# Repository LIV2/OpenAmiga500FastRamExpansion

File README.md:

# OpenAmiga500FastRamExpansion
OpenAmiga500FastRamExpansion is an Open Hardware 4/8 MB Fast RAM Expansion for the Commodore Amiga 500 Computer.

### Summary
Most low-end Amiga models only came with *Chip RAM*. "Big Box" models allowed for a different type of memory to be installed, known as *Fast RAM*, where *fast* means that it's dedicated to the main processor, so that it doesn't have to compete with the other chips in order to gain access to it (as is the case with Chip RAM). While both Chip and Fast RAM are limited in size, you can have at least a few MB of the latter on all Amigas (usually up to 8), while the former can never exceed 2 MB.

OpenAmiga500FastRamExpansion will allow you to add 4 or 8 MB of Fast RAM to your Amiga 500. This way you will be able to run more applications at once and more quickly. If you combine it with [a chip RAM expansion](http://eab.abime.net/showthread.php?t=85395), you will also be able to run almost all games supported by WHDLoad, pushing your Amiga to its limits.

OpenAmiga500FastRamExpansion is basically a clone of [a RAM expansion produced by Kipper2K a few years ago](http://eab.abime.net/showthread.php?t=64218), based on [an earlier design by lvd/NedoPC](http://lvd.nedopc.com/Projects/a600_8mb/index.html). He has since stopped producing and selling these cards and I thought it was a pity that he didn't open his designs and actually took all of them down, as this card is quite cheap to build and really useful. So I set about recreating it from scratch.

### Memory Compatibility
The required RAM Type is 16 Mbit (1M×16) DRAM in the SOJ-42 package with up to 70-80 ns access time. It is 5v-only DRAM (not SD(!)RAM) often found in old 72-pin SIMMs, EDO chips might work or not. All chips having *8160* in their part number should be OK.

|Model          |Maker             |Tested             |Working            |Data Sheet                                                                                                                                                                 |Notes                                                                                |
|---------------|------------------|:-----------------:|:-----------------:|:-------------------------------------------------------------------------------------------------------------------------------------------------------------------------:|-------------------------------------------------------------------------------------|
|AS4C1M116E5    |Alliance          |||                                                                                                                                                                           |Tested by @Homer799                                                                  |
|GM71C18160     |Hynix/LGS         |||                                                                    |Tested by lvd in his original project                                                |
|HY5118164B     |Hynix             |||                                                                                                                                                                           |Tested by @Sgw32                                                                     |
|KM416C1200AJ   |SEC               |||                                                                                                                                                                           |Reported working by Ronald Baer                                                      |
|KM416C1204AJ/BJ|SEC               |||                                             |Reported working by screwbreaker                                                     |
|MSM5118160     |OKI               |||                                                                    |Tested by lvd in his original project                                                |
|TMS41860DZ     |Texas Instruments |||                                                                                                                                                                           |Reported working by Ronald Baer                                                      |
|TMS41869DZ     |Texas Instruments |  |                   |                                                                                                                                                                           |                                                                                     |
|4218160        |NEC               |||                                                                                                                                                                           |Reported working by Ronald Baer                                                      |
|4218165        |NEC               |||                          |Tested by SukkoPera                                                                  |
|VG2618165BJ    |Vanguard          |||                                                                                                                                                                           |Tested by @Csordi                                                                    |
|NN5118160AJ-60 |NPN               |||                                                                                                                                                                           |Tested by @RipZ                                                                      |

RAM chips can either be soldered directly to the board or installed in sockets. While soldering the chips might not be trivial for the unexperienced, sockets for the SOJ-42 package are hard to find and not really easier to solder either, so the choice is up to you.

### Assembly and Installation
Normally it is not necessary to mount all the decoupling capacitors. I usually skip C4, C5, C9, C12, C15 and C18. Maybe C1 can be left out as well if you have a good power supply, your choice. R4 must be chosen according to the particular led you will be using for LD1. Actually you are free to skip LD1 and R4 altogether, if you hate power LEDs.

After everything has been soldered, you will need to program the CPLD. Whenever you do so, **make sure to carefully remove the board from your Amiga, or you might risk damaging it**. You can find the firmware [here](firmware/V2), along with instructions on how to flash it. You can provide power through the pads of C1 if you need to do so.

Make sure to use the [correct firmware version](#Firmware), according to how many chips you soldered on the board! For the 4 MB version, solder U7 and U8 only and use the dedicated firmware.

When assembly is complete, open your A500 and remove the top shield. Carefully remove the CPU (largest chip at bottom left of the board), using a chip extractor or a small flat screwdriver, taking care not to break/bend any pins. Plug it on the board, matching the orientation, and plug the whole board in the CPU socket.

Before reassembling your case, I recommend to run [SysTest/Amiga Test Kit](https://github.com/keirf/Amiga-Stuff). Use the Memory option (<kbd>F1</kbd>), it must show 4/8 MB of Fast RAM. Then start the Memory Test (<kbd>F1</kbd> again) and let it run for 50-100 rounds: if it doesn't find any errors, you are probably good to go. If you get any errors, check your solder joints, starting from actual the RAM chips, as the SOJ package is not very hand-soldering-friendly.

### Firmware
If you are using Kickstart 2.x or higher you should use the latest V2 firmware [here](firmware/V2) noting that it requires an ATF1504AS rather than the older version's ATF1502

If you are using Kickstart 1.3 you will need to use the [V1 Firmware here](firmware/V1)

#### V2 Firmware new features
Thanks to two new features this board is compatible with other autoconfig devices and should no longer cause any conflicts
* Autoconfig snooping - This board will configure itself after every other Autoconfig device
* Autosizing - The firmware will shrink the configured size automatically to make it fit within the remaining free memory pool (8M/4M/2M/1M).

#### V1 Firmware Limitations
The V1 Firmware for OpenAmiga500FastRamExpansion only has a partial implementation of the AutoConfig protocol. This has the following consequences:
- On the A500 it will only work if nothing is connected to the side expansion port (or if whatever is connected does NOT use AutoConfig).
- On the A2000 it will only work if nothing is installed in the Zorro expansion slots (again: or if whatever you installed there does not use AutoConfig).
- On the CDTV it just won't work (since the DMAC uses AutoConfig and is built-in.)

Because of these limitations it is recommended to use the new Firmware where possible, this will allow your board to coexist with other Autoconfig devices.
If you cannot use the V2 firmware for some reason (i.e you use Kickstart 1.3) then the only way to get around these limitations is flashing an alternative firmware on the board which does not use AutoConfig, but then you will have to add the RAM manually in Workbench, using the `addmem` utility. More on this soon.

### License
The OpenAmiga500FastRamExpansion documentation, including the design itself, is copyright &copy; SukkoPera 2019.

OpenAmiga500FastRamExpansion is Open Hardware licensed under the [CERN OHL v. 1.2](http://ohwr.org/cernohl).

You may redistribute and modify this documentation under the terms of the CERN OHL v.1.2. This documentation is distributed *as is* and WITHOUT ANY EXPRESS OR IMPLIED WARRANTIES whatsoever with respect to its functionality, operability or use, including, without limitation, any implied warranties OF MERCHANTABILITY, SATISFACTORY QUALITY, FITNESS FOR A PARTICULAR PURPOSE or infringement. We expressly disclaim any liability whatsoever for any direct, indirect, consequential, incidental or special damages, including, without limitation, lost revenues, lost profits, losses resulting from business interruption or loss of data, regardless of the form of action or legal theory under which the liability may be asserted, even if advised of the possibility or likelihood of such damages.

A copy of the full license is included in file [LICENSE.pdf](LICENSE.pdf), please refer to it for applicable conditions. In order to properly deal with its terms, please see file [LICENSE_HOWTO.pdf](LICENSE_HOWTO.pdf).

The contact points for information about manufactured Products (see section 4.2) are listed in file [PRODUCT.md](PRODUCT.md).

Any modifications made by Licensees (see section 3.4.b) shall be recorded in file [CHANGES.md](CHANGES.md).

The Documentation Location of the original project is https://github.com/SukkoPera/OpenAmiga500FastRamExpansion/.

### Support the Project
Since the project is open you are free to get the PCBs made by your preferred manufacturer, however in case you want to support the development, you can order them from PCBWay through this link:

You get my gratitude and cheap, professionally-made and good quality PCBs, I get some credit that will help with this and [other projects](https://www.pcbway.com/project/member/shareproject/?bmbid=41100). You won't even have to worry about the various PCB options, it's all pre-configured for you!

Also, if you still have to register to that site, [you can use this link](https://www.pcbway.com/setinvite.aspx?inviteid=41100) to get some bonus initial credit (and yield me some more).

Again, if you want to use another manufacturer, feel free to, don't feel obligated :). But then you can buy me a coffee if you want:

### Thanks
- lvd for the initial design and the support he gave me during development
- Kipper2K for making his boards
- majinga for helping with the testing

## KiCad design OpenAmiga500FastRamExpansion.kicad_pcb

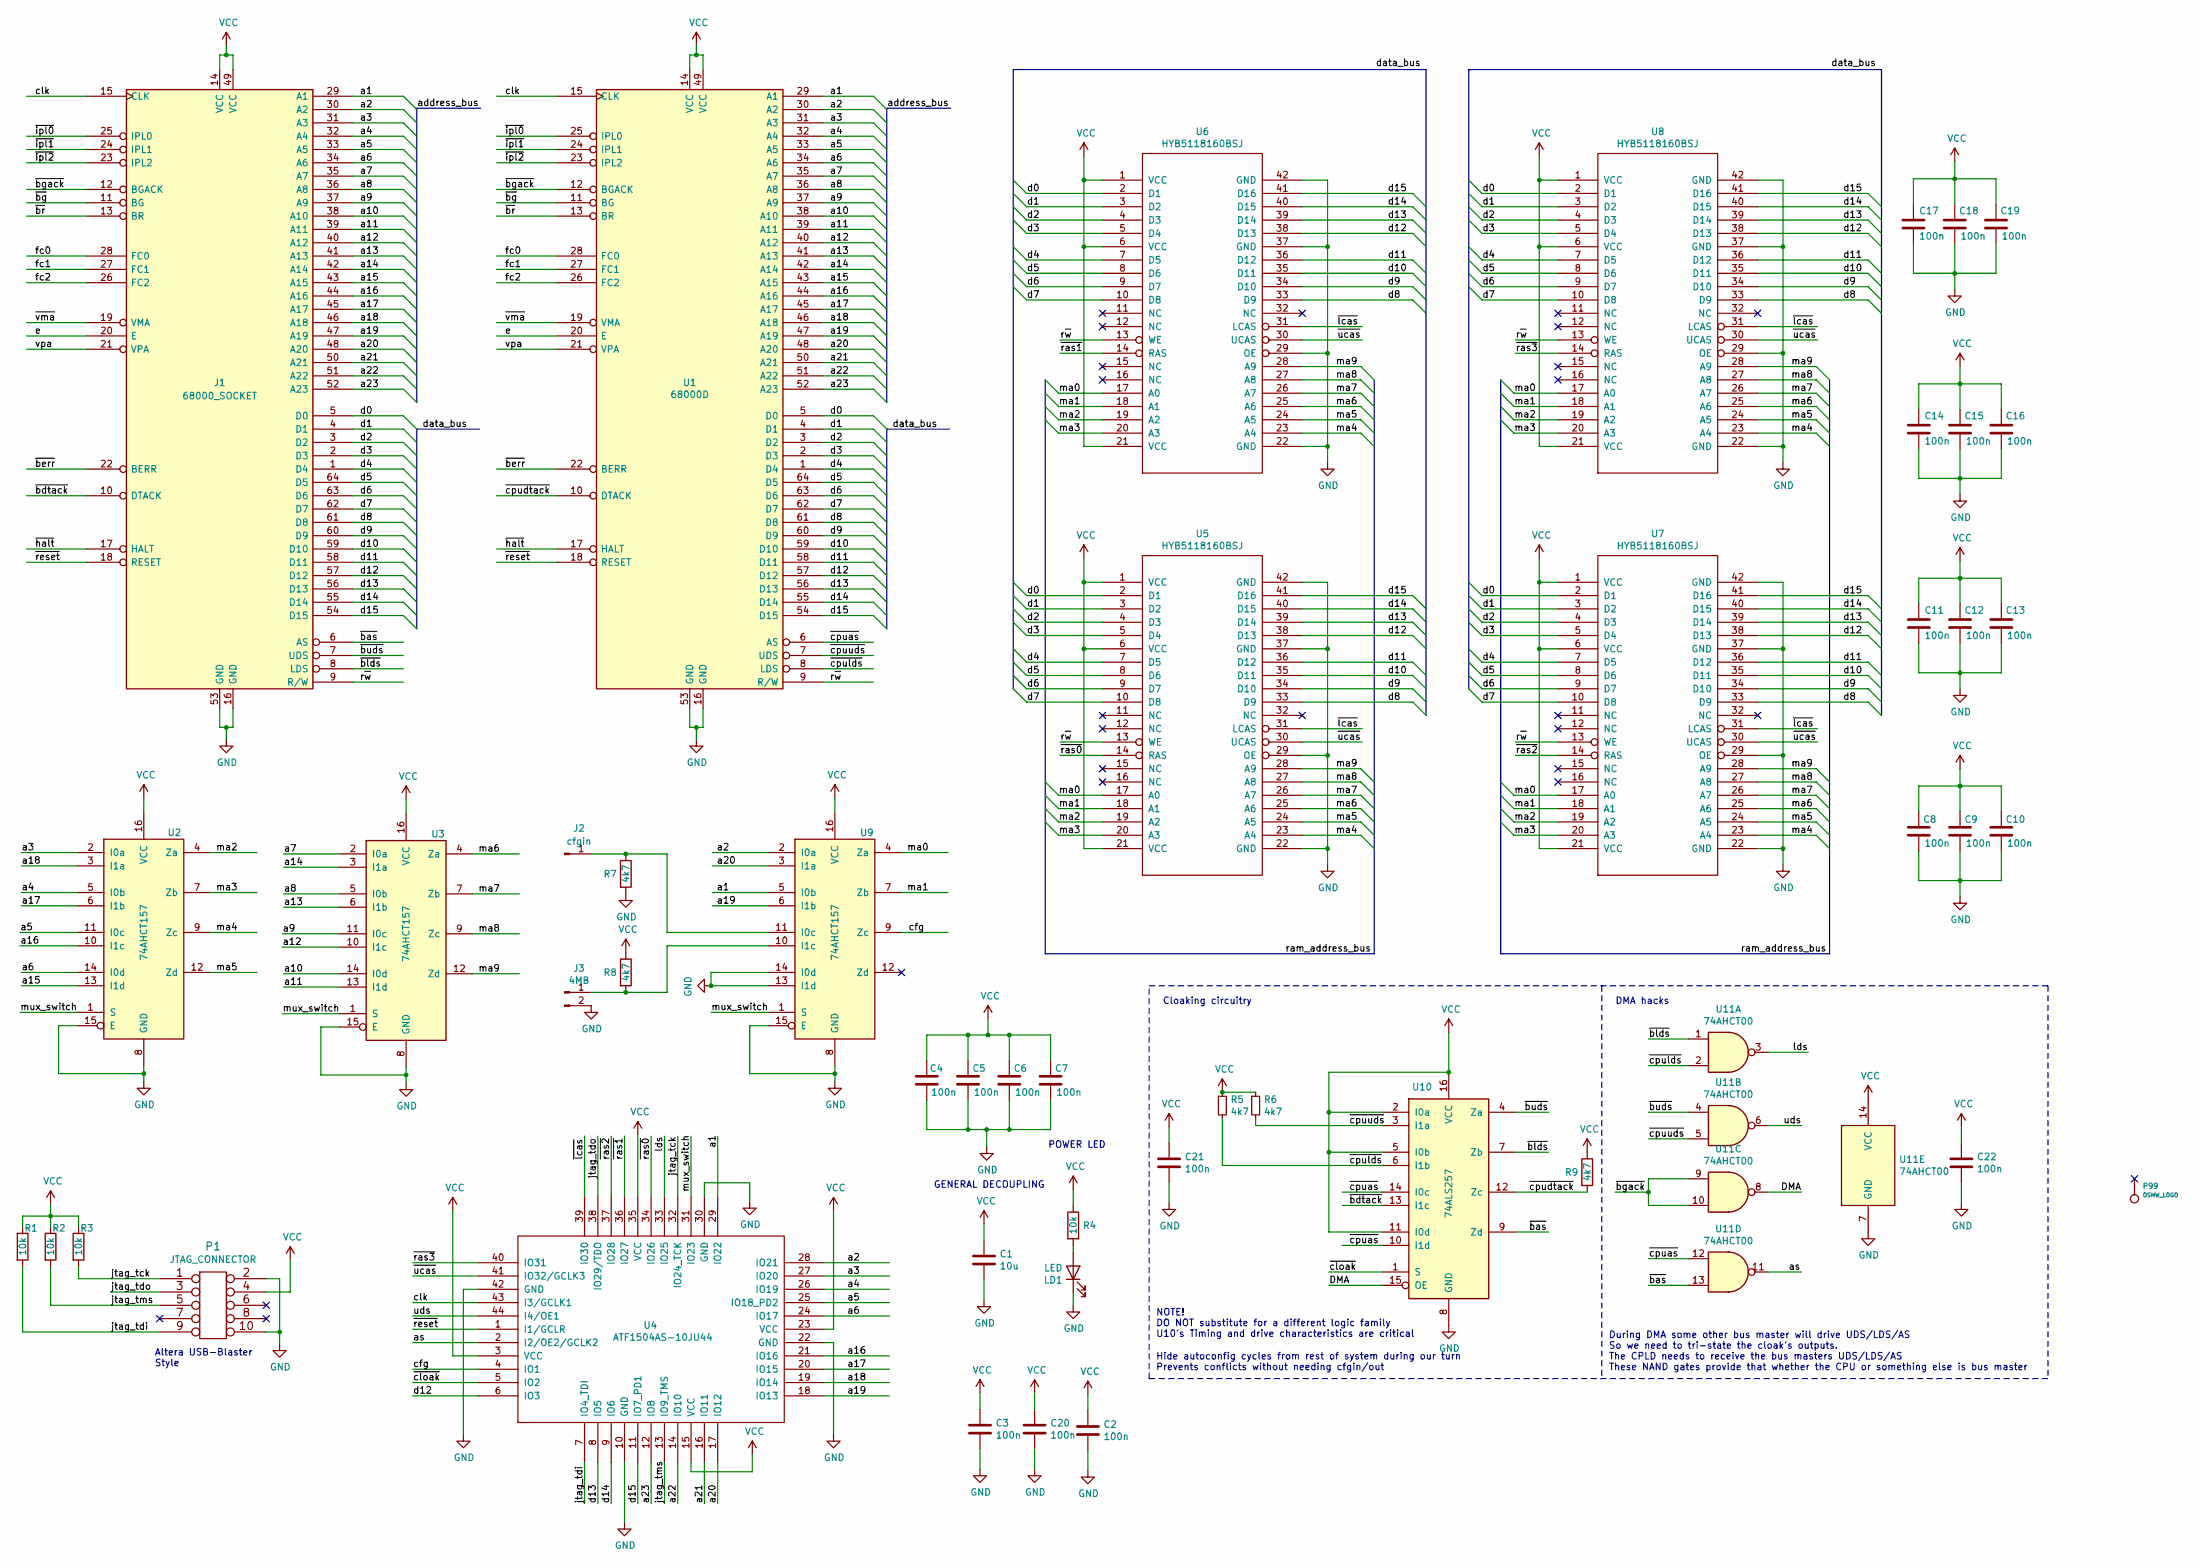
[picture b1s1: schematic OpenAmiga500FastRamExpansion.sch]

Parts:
C1: 10u; CP_Radial_D5.0mm_P2.00mm
C2, C3, C4, C5, C6, C7, C8, C9, C10, C11, C12, C13, C14, C15, C16, C17, C18, C19: 100n; C_0805_2012Metric_Pad1.15x1.40mm_HandSolder
C20, C21, C22: 100n; C_0805_2012Metric_Pad1.18x1.45mm_HandSolder
J1: 68000_SOCKET; DIP-64_W22.86mm_Socket_LongPads_Socket
J2: cfgin; PinHeader_1x01_P2.54mm_Horizontal
J3: 4MB; PinHeader_1x02_P2.54mm_Horizontal
LD1: LED; LED_0805_HandSoldering_ModSilkS
P1: JTAG_CONNECTOR; IDC-Header_2x05_P2.54mm_Vertical
P99: OSHW_LOGO; OSHW-Logo2_7.3x6mm_Copper
R1, R2, R3, R4: 10k; R_0805_2012Metric_Pad1.15x1.40mm_HandSolder
R5, R6, R7, R8, R9: 4k7; R_0805_2012Metric_Pad1.20x1.40mm_HandSolder
U1: 68000D; DIP-64_W22.86mm_Socket_LongPads_IC
U2, U3, U9: 74AHCT157; SOIC-16_3.9x9.9mm_P1.27mm
U4: ATF1504AS-10JU44; PLCC-44_THT-Socket
U5, U6, U7, U8: HYB5118160BSJ; SOJ-42-LongPads
U10: 74ALS257; SOIC-16_3.9x9.9mm_P1.27mm
U11: 74AHCT00; SOIC-14_3.9x8.7mm_P1.27mm

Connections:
/DMA: U10.15 (OE), U11.8
/a1: J1.29 (A1), U1.29 (A1), U4.29 (IO22), U9.5 (I0b)
/a2: J1.30 (A2), U1.30 (A2), U4.28 (IO21), U9.2 (I0a)
/a3: J1.31 (A3), U1.31 (A3), U2.2 (I0a), U4.27 (IO20)
/a4: J1.32 (A4), U1.32 (A4), U2.5 (I0b), U4.26 (IO19)
/a5: J1.33 (A5), U1.33 (A5), U2.11 (I0c), U4.25 (IO18_PD2)
/a6: J1.34 (A6), U1.34 (A6), U2.14 (I0d), U4.24 (IO17)
/a7: J1.35 (A7), U1.35 (A7), U3.2 (I0a)
/a8: J1.36 (A8), U1.36 (A8), U3.5 (I0b)
/a9: J1.37 (A9), U1.37 (A9), U3.11 (I0c)
/a10: J1.38 (A10), U1.38 (A10), U3.14 (I0d)
/a11: J1.39 (A11), U1.39 (A11), U3.13 (I1d)
/a12: J1.40 (A12), U1.40 (A12), U3.10 (I1c)
/a13: J1.41 (A13), U1.41 (A13), U3.6 (I1b)
/a14: J1.42 (A14), U1.42 (A14), U3.3 (I1a)
/a15: J1.43 (A15), U1.43 (A15), U2.13 (I1d)
/a16: J1.44 (A16), U1.44 (A16), U2.10 (I1c), U4.21 (IO16)
/a17: J1.45 (A17), U1.45 (A17), U2.6 (I1b), U4.20 (IO15)
/a18: J1.46 (A18), U1.46 (A18), U2.3 (I1a), U4.19 (IO14)
/a19: J1.47 (A19), U1.47 (A19), U4.18 (IO13), U9.6 (I1b)
/a20: J1.48 (A20), U1.48 (A20), U4.17 (IO12), U9.3 (I1a)
/a21: J1.50 (A21), U1.50 (A21), U4.16 (IO11)
/a22: J1.51 (A22), U1.51 (A22), U4.14 (IO10)
/a23: J1.52 (A23), U1.52 (A23), U4.12 (IO8)
/as: U4.2 (I2/OE2/GCLK2), U11.11
/cfg: U4.4 (IO1), U9.9 (Zc)
/clk: J1.15 (CLK), U1.15 (CLK), U4.43 (I3/GCLK1)
/d0: J1.5 (D0), U1.5 (D0), U5.2 (D1), U6.2 (D1), U7.2 (D1), U8.2 (D1)
/d1: J1.4 (D1), U1.4 (D1), U5.3 (D2), U6.3 (D2), U7.3 (D2), U8.3 (D2)
/d2: J1.3 (D2), U1.3 (D2), U5.4 (D3), U6.4 (D3), U7.4 (D3), U8.4 (D3)
/d3: J1.2 (D3), U1.2 (D3), U5.5 (D4), U6.5 (D4), U7.5 (D4), U8.5 (D4)
/d4: J1.1 (D4), U1.1 (D4), U5.7 (D5), U6.7 (D5), U7.7 (D5), U8.7 (D5)
/d5: J1.64 (D5), U1.64 (D5), U5.8 (D6), U6.8 (D6), U7.8 (D6), U8.8 (D6)
/d6: J1.63 (D6), U1.63 (D6), U5.9 (D7), U6.9 (D7), U7.9 (D7), U8.9 (D7)
/d7: J1.62 (D7), U1.62 (D7), U5.10 (D8), U6.10 (D8), U7.10 (D8), U8.10 (D8)
/d8: J1.61 (D8), U1.61 (D8), U5.33 (D9), U6.33 (D9), U7.33 (D9), U8.33 (D9)
/d9: J1.60 (D9), U1.60 (D9), U5.34 (D10), U6.34 (D10), U7.34 (D10), U8.34 (D10)
/d10: J1.59 (D10), U1.59 (D10), U5.35 (D11), U6.35 (D11), U7.35 (D11), U8.35 (D11)
/d11: J1.58 (D11), U1.58 (D11), U5.36 (D12), U6.36 (D12), U7.36 (D12), U8.36 (D12)
/d12: J1.57 (D12), U1.57 (D12), U4.6 (IO3), U5.38 (D13), U6.38 (D13), U7.38 (D13), U8.38 (D13)
/d13: J1.56 (D13), U1.56 (D13), U4.8 (IO5), U5.39 (D14), U6.39 (D14), U7.39 (D14), U8.39 (D14)
/d14: J1.55 (D14), U1.55 (D14), U4.9 (IO6), U5.40 (D15), U6.40 (D15), U7.40 (D15), U8.40 (D15)
/d15: J1.54 (D15), U1.54 (D15), U4.11 (IO7_PD1), U5.41 (D16), U6.41 (D16), U7.41 (D16), U8.41 (D16)
/e: J1.20 (E), U1.20 (E)
/fc0: J1.28 (FC0), U1.28 (FC0)
/fc1: J1.27 (FC1), U1.27 (FC1)
/fc2: J1.26 (FC2), U1.26 (FC2)
/jtag_tck: P1.1, R3.2, U4.32 (IO24_TCK)
/jtag_tdi: P1.9, R1.2, U4.7 (IO4_TDI)
/jtag_tdo: P1.3, U4.38 (IO29/TDO)
/jtag_tms: P1.5, R2.2, U4.13 (IO9_TMS)
/lds: U4.33 (IO25), U11.3
/ma0: U5.17 (A0), U6.17 (A0), U7.17 (A0), U8.17 (A0), U9.4 (Za)
/ma1: U5.18 (A1), U6.18 (A1), U7.18 (A1), U8.18 (A1), U9.7 (Zb)
/ma2: U2.4 (Za), U5.19 (A2), U6.19 (A2), U7.19 (A2), U8.19 (A2)
/ma3: U2.7 (Zb), U5.20 (A3), U6.20 (A3), U7.20 (A3), U8.20 (A3)
/ma4: U2.9 (Zc), U5.23 (A4), U6.23 (A4), U7.23 (A4), U8.23 (A4)
/ma5: U2.12 (Zd), U5.24 (A5), U6.24 (A5), U7.24 (A5), U8.24 (A5)
/ma6: U3.4 (Za), U5.25 (A6), U6.25 (A6), U7.25 (A6), U8.25 (A6)
/ma7: U3.7 (Zb), U5.26 (A7), U6.26 (A7), U7.26 (A7), U8.26 (A7)
/ma8: U3.9 (Zc), U5.27 (A8), U6.27 (A8), U7.27 (A8), U8.27 (A8)
/ma9: U3.12 (Zd), U5.28 (A9), U6.28 (A9), U7.28 (A9), U8.28 (A9)
/mux_switch: U2.1 (S), U3.1 (S), U4.31 (IO23), U9.1 (S)
/r~w: J1.9 (R/W), U1.9 (R/W), U5.13 (WE), U6.13 (WE), U7.13 (WE), U8.13 (WE)
/uds: U4.44 (I4/OE1), U11.6
/vpa: J1.21 (VPA), U1.21 (VPA)
/~bas: J1.6 (AS), U10.9 (Zd), U11.13
/~bdtack: J1.10 (DTACK), U10.13 (I1c)
/~berr: J1.22 (BERR), U1.22 (BERR)
/~bg: J1.11 (BG), U1.11 (BG)
/~bgack: J1.12 (BGACK), U1.12 (BGACK), U11.9, U11.10
/~blds: J1.8 (LDS), U10.7 (Zb), U11.1
/~br: J1.13 (BR), U1.13 (BR)
/~buds: J1.7 (UDS), U10.4 (Za), U11.4
/~cloak: U4.5 (IO2), U10.1 (S)
/~cpuas: U1.6 (AS), U10.10 (I1d), U10.14 (I0c), U11.12
/~cpudtack: R9.2, U1.10 (DTACK), U10.12 (Zc)
/~cpulds: R5.2, U1.8 (LDS), U10.6 (I1b), U11.2
/~cpuuds: R6.2, U1.7 (UDS), U10.3 (I1a), U11.5
/~halt: J1.17 (HALT), U1.17 (HALT)
/~ipl0: J1.25 (IPL0), U1.25 (IPL0)
/~ipl1: J1.24 (IPL1), U1.24 (IPL1)
/~ipl2: J1.23 (IPL2), U1.23 (IPL2)
/~lcas: U4.39 (IO30), U5.31 (LCAS), U6.31 (LCAS), U7.31 (LCAS), U8.31 (LCAS)
/~ras0: U4.34 (IO26), U5.14 (RAS)
/~ras1: U4.36 (IO27), U6.14 (RAS)
/~ras2: U4.37 (IO28), U7.14 (RAS)
/~ras3: U4.40 (IO31), U8.14 (RAS)
/~reset: J1.18 (RESET), U1.18 (RESET), U4.1 (I1/GCLR)
/~ucas: U4.41 (IO32/GCLK3), U5.30 (UCAS), U6.30 (UCAS), U7.30 (UCAS), U8.30 (UCAS)
/~vma: J1.19 (VMA), U1.19 (VMA)
GND: C1.2, C2.2, C3.2, C4.2, C5.2, C6.2, C7.2, C8.2, C9.2, C10.2, C11.2, C12.2, C13.2, C14.2, C15.2, C16.2, C17.2, C18.2, C19.2, C20.2, C21.2, C22.2, J1.16 (GND), J1.53 (GND), J3.2, LD1.1 (K), P1.2, P1.10, R7.2, U1.16 (GND), U1.53 (GND), U2.8 (GND), U2.15 (E), U3.8 (GND), U3.15 (E), U4.10 (GND), U4.22 (GND), U4.30 (GND), U4.42 (GND), U5.22 (GND), U5.29 (OE), U5.37 (GND), U5.42 (GND), U6.22 (GND), U6.29 (OE), U6.37 (GND), U6.42 (GND), U7.22 (GND), U7.29 (OE), U7.37 (GND), U7.42 (GND), U8.22 (GND), U8.29 (OE), U8.37 (GND), U8.42 (GND), U9.8 (GND), U9.13 (I1d), U9.14 (I0d), U9.15 (E), U10.8 (GND), U11.7 (GND)
unnamed: J2.1, R7.1, U9.11 (I0c)
unnamed: J3.1, R8.2, U9.10 (I1c)
unnamed: LD1.2 (A), R4.2
VCC: C1.1, C2.1, C3.1, C4.1, C5.1, C6.1, C7.1, C8.1, C9.1, C10.1, C11.1, C12.1, C13.1, C14.1, C15.1, C16.1, C17.1, C18.1, C19.1, C20.1, C21.1, C22.1, J1.14 (VCC), J1.49 (VCC), P1.4, R1.1, R2.1, R3.1, R4.1, R5.1, R6.1, R8.1, R9.1, U1.14 (VCC), U1.49 (VCC), U2.16 (VCC), U3.16 (VCC), U4.3 (VCC), U4.15 (VCC), U4.23 (VCC), U4.35 (VCC), U5.1 (VCC), U5.6 (VCC), U5.21 (VCC), U6.1 (VCC), U6.6 (VCC), U6.21 (VCC), U7.1 (VCC), U7.6 (VCC), U7.21 (VCC), U8.1 (VCC), U8.6 (VCC), U8.21 (VCC), U9.16 (VCC), U10.2 (I0a), U10.5 (I0b), U10.11 (I0d), U10.16 (VCC), U11.14 (VCC)

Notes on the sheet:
Altera USB-Blaster Style
Cloaking circuitry
DMA hacks
Hide autoconfig cycles from rest of system during our turn Prevents conflicts without needing cfgin/out
During DMA some other bus master will drive UDS/LDS/AS So we need to tri-state the cloak's outputs. The CPLD needs to receive the bus masters UDS/LDS/AS These NAND gates provide that whether the CPU or something else is bus master
GENERAL DECOUPLING
POWER LED
NOTE! DO NOT substitute for a different logic family U10's Timing and drive characteristics are critical

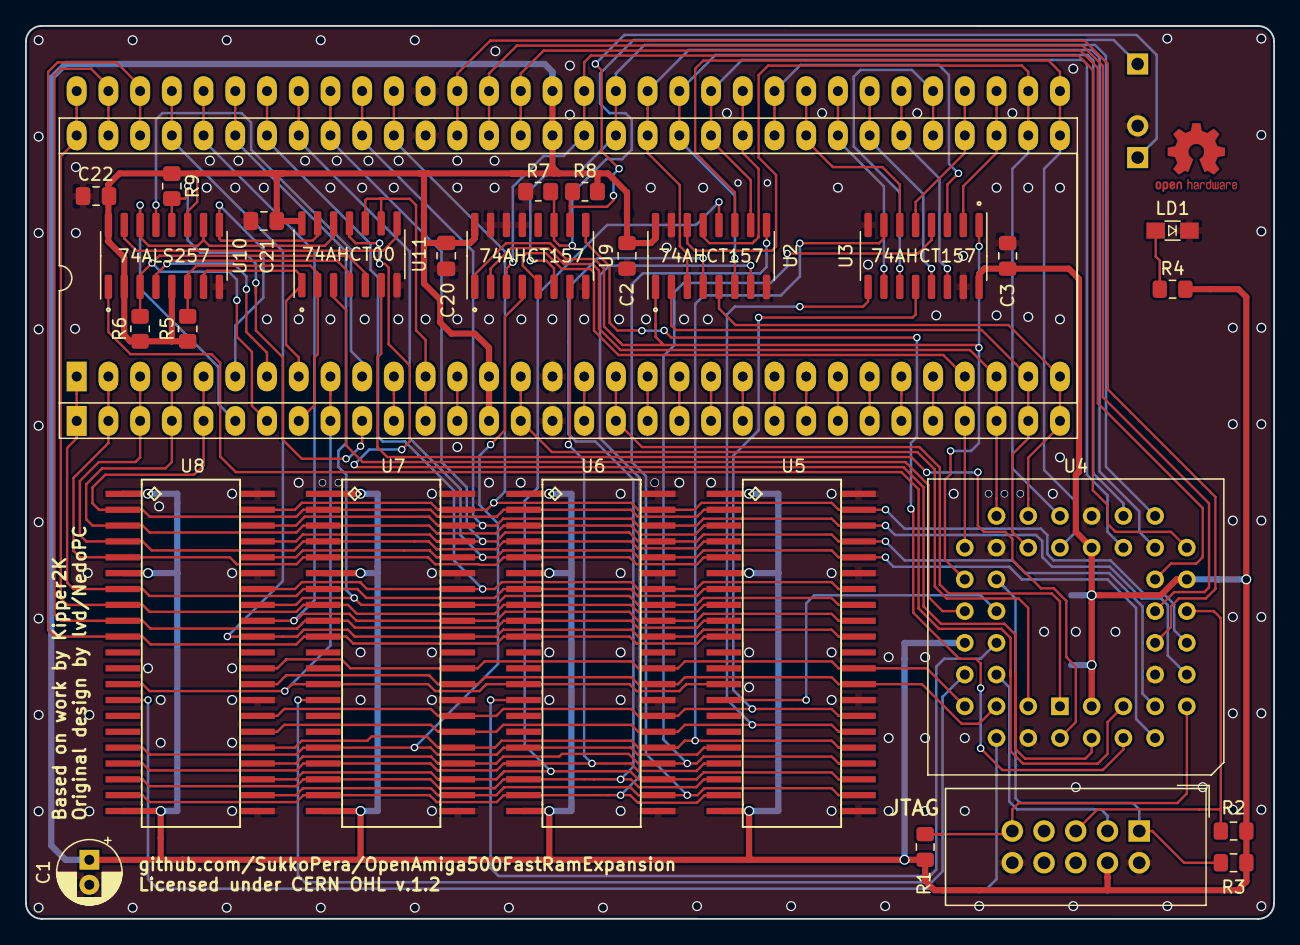
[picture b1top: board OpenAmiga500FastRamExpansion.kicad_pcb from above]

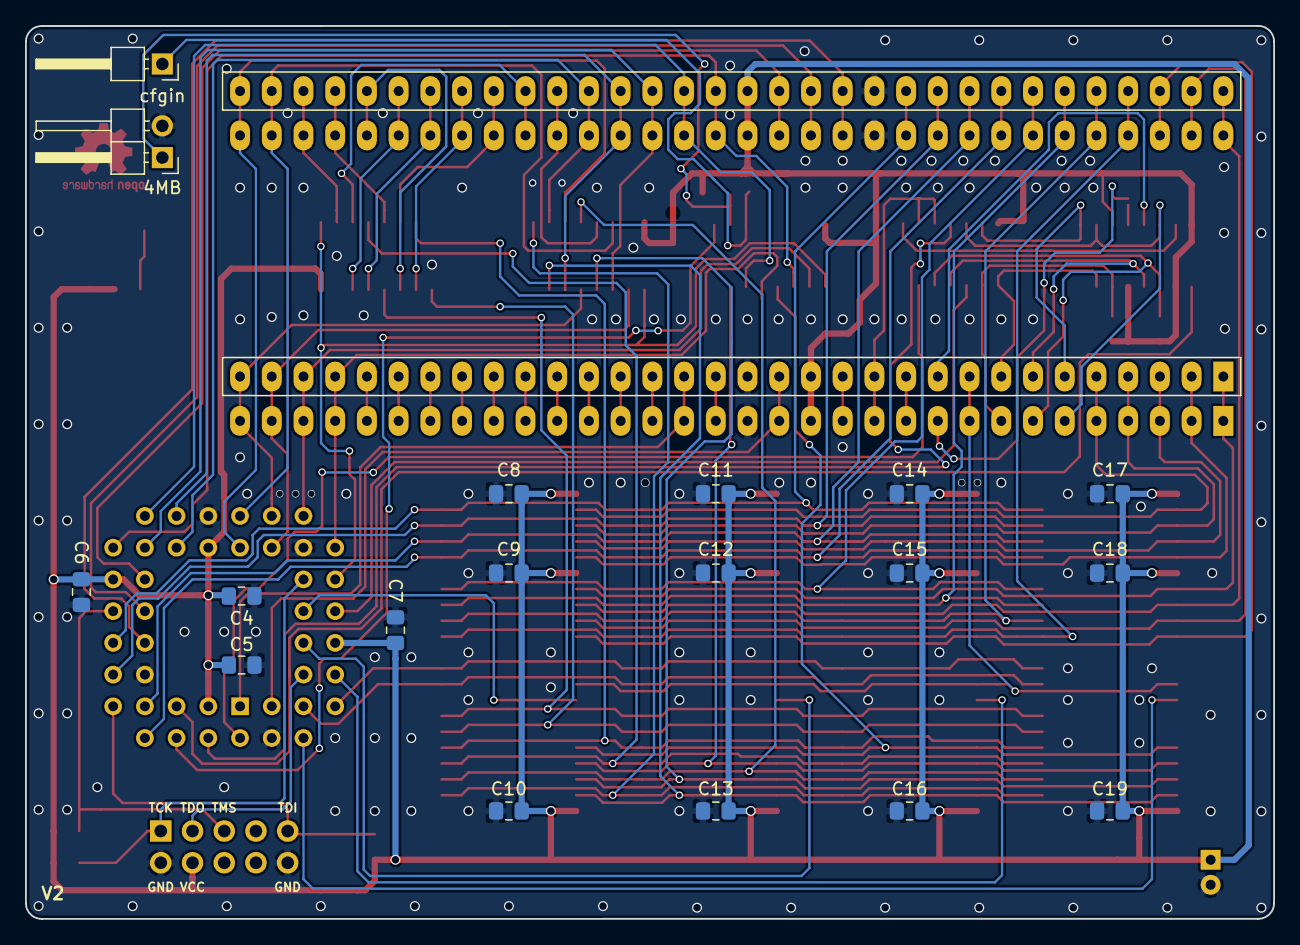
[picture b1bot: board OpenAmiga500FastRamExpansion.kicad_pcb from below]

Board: 2 copper layers, 100.0 x 71.5 mm, 48 parts (18 on the bottom side), 96 nets.

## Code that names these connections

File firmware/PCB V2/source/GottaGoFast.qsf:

# -------------------------------------------------------------------------- #
#
# Copyright (C) 1991-2013 Altera Corporation
# Your use of Altera Corporation's design tools, logic functions 
# and other software and tools, and its AMPP partner logic 
# functions, and any output files from any of the foregoing 
# (including device programming or simulation files), and any 
# associated documentation or information are expressly subject 
# to the terms and conditions of the Altera Program License 
# Subscription Agreement, Altera MegaCore Function License 
# Agreement, or other applicable license agreement, including, 
# without limitation, that your use is for the sole purpose of 
# programming logic devices manufactured by Altera and sold by 
# Altera or its authorized distributors.  Please refer to the 
# applicable agreement for further details.
#
# -------------------------------------------------------------------------- #
#
# Quartus II 64-Bit
# Version 13.0.1 Build 232 06/12/2013 Service Pack 1 SJ Web Edition
# Date created = 09:31:48  January 28, 2021
#
# -------------------------------------------------------------------------- #
#
# Notes:
#
# 1) The default values for assignments are stored in the file:
#		GottaGoFast_assignment_defaults.qdf
#    If this file doesn't exist, see file:
#		assignment_defaults.qdf
#
# 2) Altera recommends that you do not modify this file. This
#    file is updated automatically by the Quartus II software
#    and any changes you make may be lost or overwritten.
#
# -------------------------------------------------------------------------- #


set_global_assignment -name FAMILY MAX7000S
set_global_assignment -name DEVICE "EPM7064SLC44-10"
set_global_assignment -name TOP_LEVEL_ENTITY GottaGoFast
set_global_assignment -name ORIGINAL_QUARTUS_VERSION "13.0 SP1"
set_global_assignment -name PROJECT_CREATION_TIME_DATE "09:31:48  JANUARY 28, 2021"
set_global_assignment -name LAST_QUARTUS_VERSION "13.0 SP1"
set_global_assignment -name PROJECT_OUTPUT_DIRECTORY output_files
set_global_assignment -name DEVICE_FILTER_PACKAGE PLCC
set_global_assignment -name DEVICE_FILTER_PIN_COUNT 44
set_global_assignment -name DEVICE_FILTER_SPEED_GRADE 10
set_global_assignment -name ERROR_CHECK_FREQUENCY_DIVISOR "-1"
set_global_assignment -name EDA_SIMULATION_TOOL "ModelSim-Altera (Verilog)"
set_global_assignment -name EDA_OUTPUT_DATA_FORMAT "VERILOG HDL" -section_id eda_simulation
set_global_assignment -name MAX7000_DEVICE_IO_STANDARD TTL
set_location_assignment PIN_1 -to RESETn
set_location_assignment PIN_4 -to CFGINn
set_location_assignment PIN_5 -to CLOAKn
set_location_assignment PIN_6 -to DBUS[12]
set_location_assignment PIN_8 -to DBUS[13]
set_location_assignment PIN_9 -to DBUS[14]
set_location_assignment PIN_11 -to DBUS[15]
set_location_assignment PIN_12 -to ADDR_HI[23]
set_location_assignment PIN_14 -to ADDR_HI[22]
set_location_assignment PIN_16 -to ADDR_HI[21]
set_location_assignment PIN_17 -to ADDR_HI[20]
set_location_assignment PIN_18 -to ADDR_HI[19]
set_location_assignment PIN_19 -to ADDR_HI[18]
set_location_assignment PIN_20 -to ADDR_HI[17]
set_location_assignment PIN_21 -to ADDR_HI[16]
set_location_assignment PIN_24 -to ADDR_LO[6]
set_location_assignment PIN_25 -to ADDR_LO[5]
set_location_assignment PIN_26 -to ADDR_LO[4]
set_location_assignment PIN_27 -to ADDR_LO[3]
set_location_assignment PIN_28 -to ADDR_LO[2]
set_location_assignment PIN_29 -to ADDR_LO[1]
set_location_assignment PIN_43 -to CLK
set_location_assignment PIN_39 -to LCASn
set_location_assignment PIN_33 -to LDS
set_location_assignment PIN_34 -to RAS0n
set_location_assignment PIN_36 -to RAS1n
set_location_assignment PIN_37 -to RAS2n
set_location_assignment PIN_40 -to RAS3n
set_location_assignment PIN_31 -to mux_switch
set_location_assignment PIN_41 -to UCASn
set_location_assignment PIN_44 -to UDS
set_global_assignment -name VERILOG_TEST_BENCH_FILE simulation/modelsim/GottaGoFast.vt
set_global_assignment -name VERILOG_FILE GottaGoFast.v
set_global_assignment -name EDA_TIME_SCALE "1 ps" -section_id eda_simulation
set_global_assignment -name EDA_TEST_BENCH_ENABLE_STATUS TEST_BENCH_MODE -section_id eda_simulation
set_global_assignment -name EDA_NATIVELINK_SIMULATION_TEST_BENCH GottaGoFast_vlg_tst -section_id eda_simulation
set_global_assignment -name EDA_TEST_BENCH_NAME GottaGoFast_vlg_tst -section_id eda_simulation
set_global_assignment -name EDA_DESIGN_INSTANCE_NAME NA -section_id GottaGoFast_vlg_tst
set_global_assignment -name EDA_TEST_BENCH_MODULE_NAME GottaGoFast_vlg_tst -section_id GottaGoFast_vlg_tst
set_global_assignment -name OPTIMIZE_HOLD_TIMING OFF
set_global_assignment -name OPTIMIZE_MULTI_CORNER_TIMING OFF
set_global_assignment -name FITTER_EFFORT "STANDARD FIT"
set_global_assignment -name EDA_TEST_BENCH_FILE simulation/modelsim/GottaGoFast.vt -section_id GottaGoFast_vlg_tst
set_location_assignment PIN_32 -to TCK
set_location_assignment PIN_7 -to TDI
set_location_assignment PIN_38 -to TDO
set_location_assignment PIN_13 -to TMS
set_location_assignment PIN_2 -to AS

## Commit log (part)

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2021-02-04 Autoconfig improvements * Add CFGIN * Add hardware to hide autoconfig cycles until configured - Config before others - No need for cfgout - No need for cfgin if you want it to be the first dev config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
    As of yet untested, waiting on parts and need to adapt code :)
2021-02-13 Isolate /AS too
2021-02-14 Add V2 Firmware, update documentation
2021-02-16 Fixup schematic + documentation
2021-02-28 Remove unnecessary via
2025-01-07 Conditionally build firmware for CDTV
2025-01-08 Add CDTV Binaries
2026-02-13 Revise donation link and remove help section
    Updated the coffee donation link and removed the help section.

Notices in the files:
OpenAmiga500FastRamExpansion.kicad_pcb:
Licensed under CERN OHL v.1.2
